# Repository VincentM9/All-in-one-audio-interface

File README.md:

# All-in-one audio interface

A USB DAC / headphone amplifier with a phantom-powered microphone input,
built one block at a time. Each block is designed, drawn in Altium, built and
tested on its own before the next one starts.

## Goal

- Headphone output: **at least 2 W into 32 Ω** single-ended, plus balanced outputs (4.4 mm and 4-pin XLR)
- USB DAC for playback
- XLR microphone input with 48 V phantom power for condenser mics

## Blocks

| # | Block | Status |
|---|---|---|
| 1 | [Balanced headphone amplifier](docs/01-headphone-amp.md): line in → ~8.9 W @ 32 Ω balanced (4.4 mm + 4-pin XLR), ~2.5 W single-ended (6.35 mm), from a bench ±16 V supply | **designing** |
| 2 | Power supply: DC jack → ±16 V at 1.2 A per rail for the amp | not started |
| 3 | USB DAC: USB → line out | not started |
| 4 | Mic preamp with 48 V phantom | not started |
| 5 | Put it together: one board, one enclosure | not started |

The earlier all-in-one attempt (full schematic, generated PCB) is in git
history before this commit, if any part of it is ever useful again.

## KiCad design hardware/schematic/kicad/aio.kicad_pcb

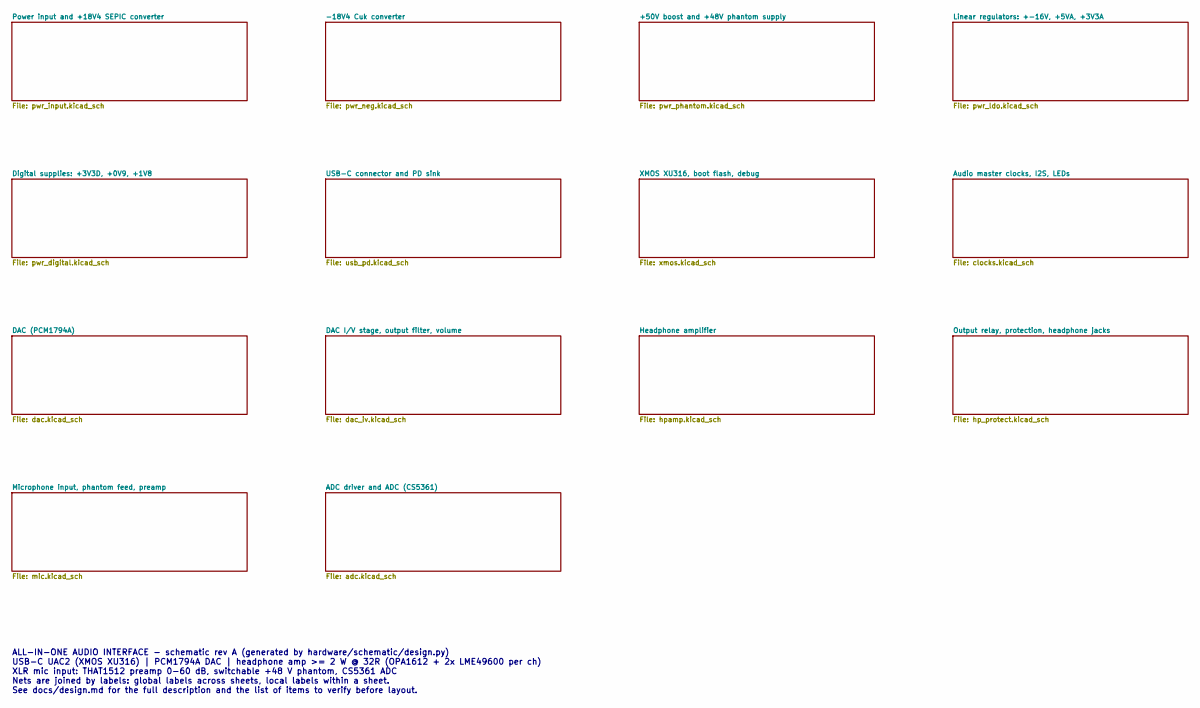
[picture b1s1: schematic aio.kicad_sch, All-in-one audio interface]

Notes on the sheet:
ALL-IN-ONE AUDIO INTERFACE - schematic rev A (generated by hardware/schematic/design.py) USB-C UAC2 (XMOS XU316) | PCM1794A DAC | headphone amp >= 2 W @ 32R (OPA1612 + 2x LME49600 per ch) XLR mic input: THAT1512 preamp 0-60 dB, switchable +48 V phantom, CS5361 ADC Nets are joined by labels: global 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

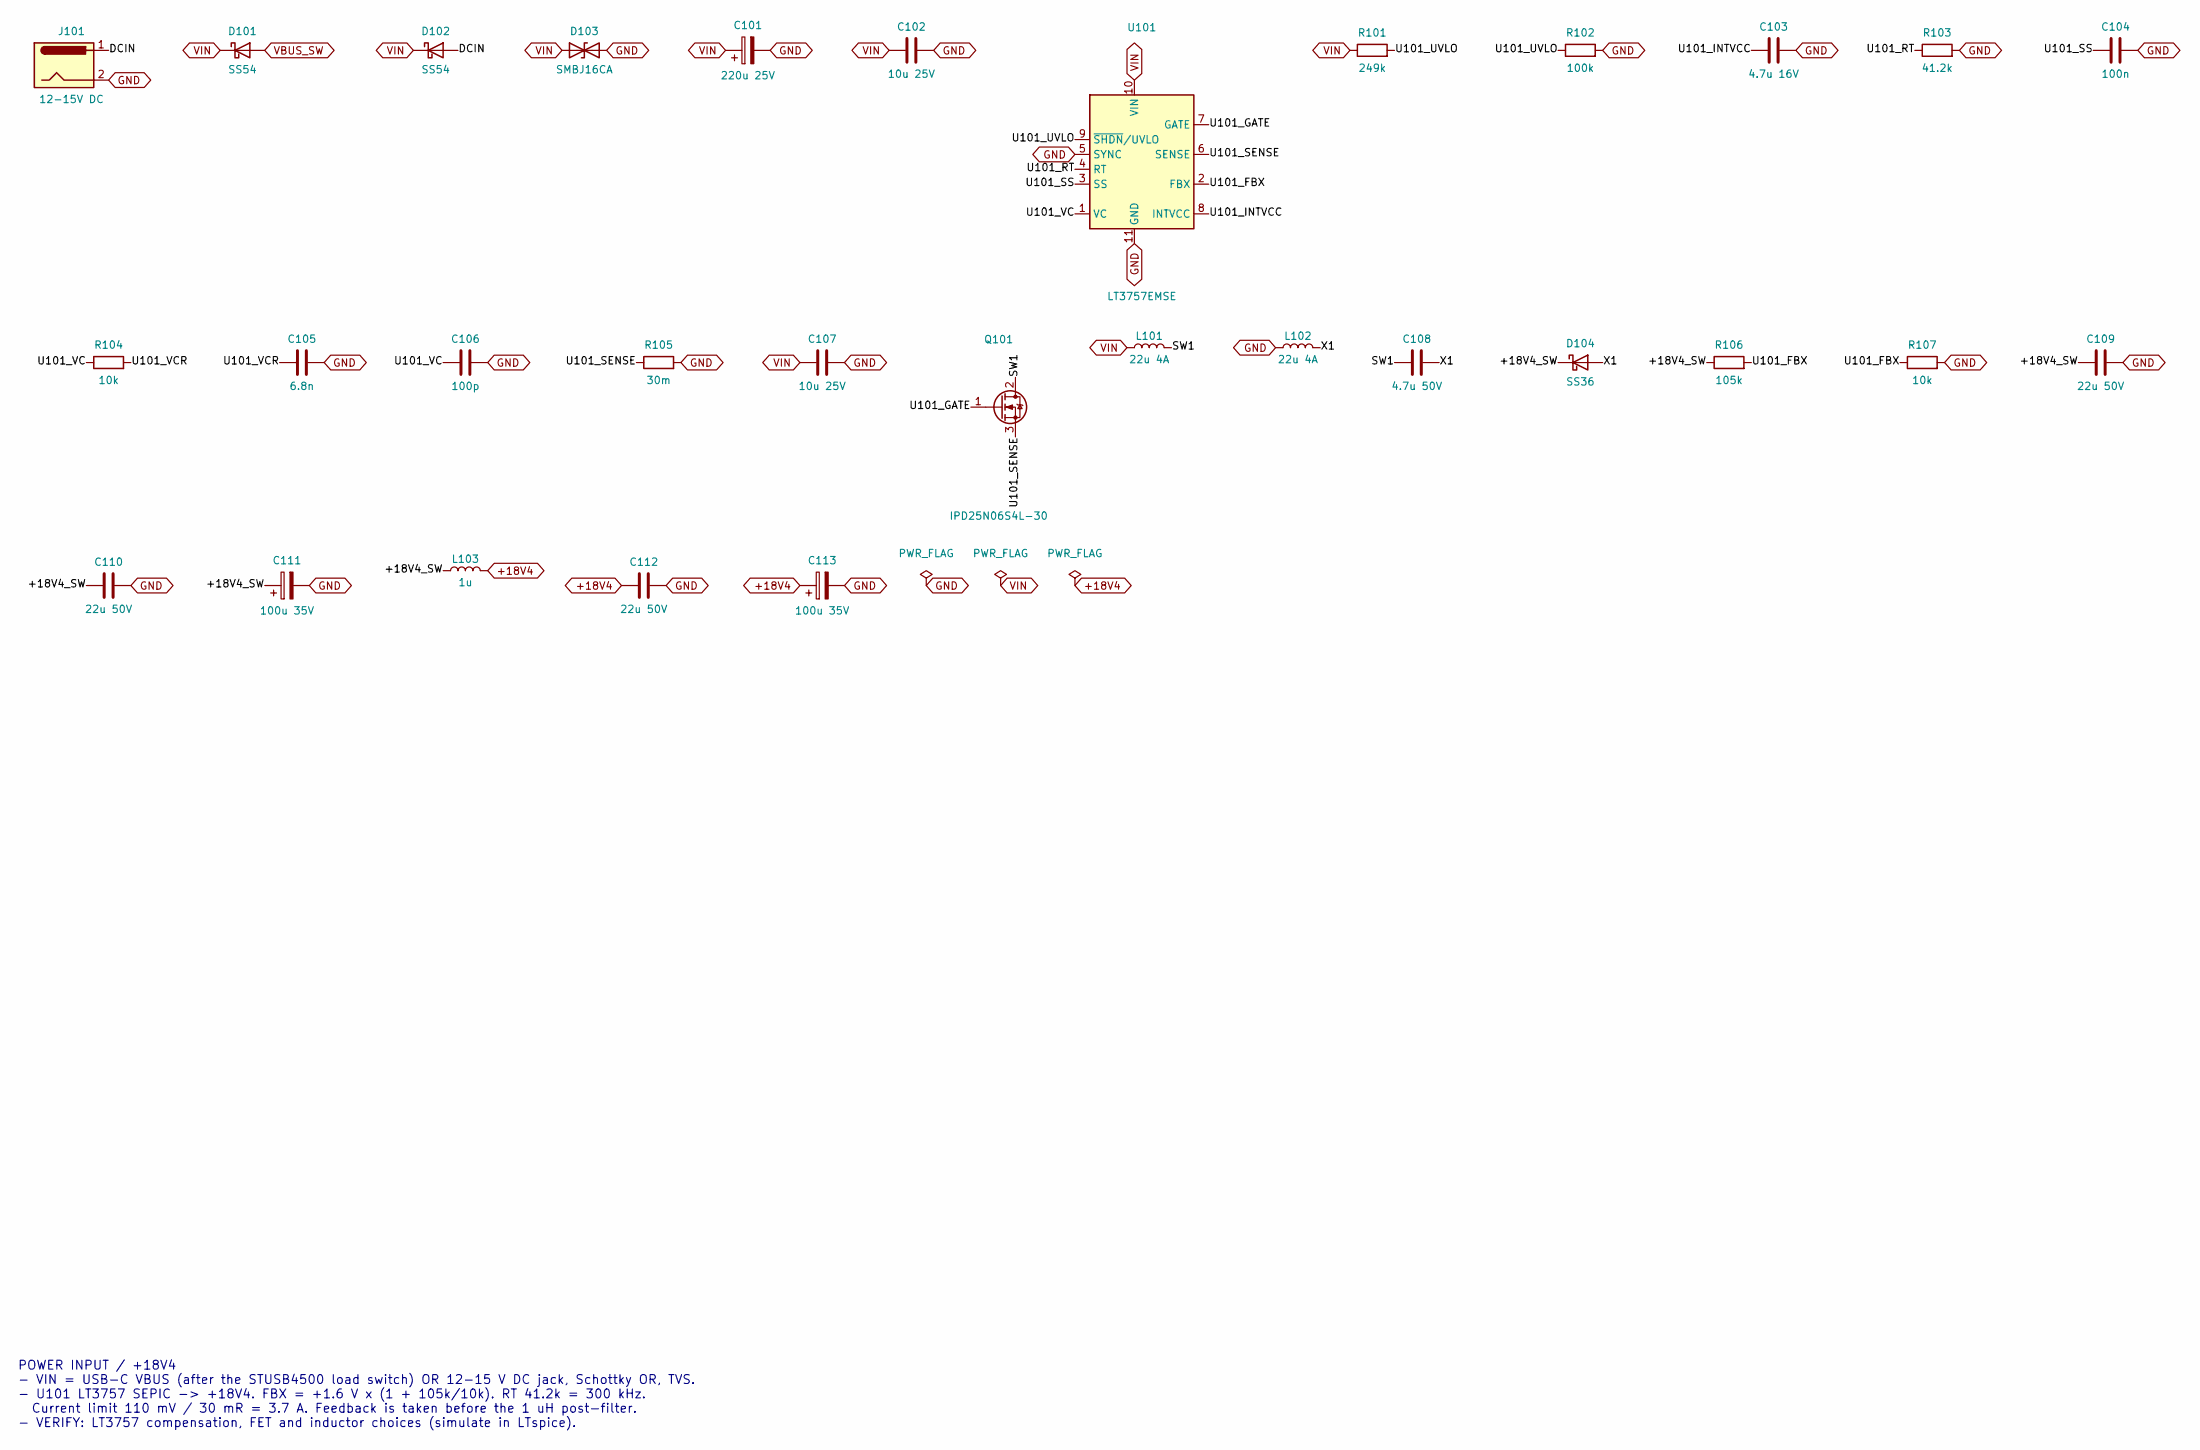
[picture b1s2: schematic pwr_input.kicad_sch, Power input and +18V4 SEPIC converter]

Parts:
C101: 220u 25V; CP_Elec_10x10
C102, C107: 10u 25V; C_1210_3225Metric
C103: 4.7u 16V; C_0805_2012Metric
C104: 100n; C_0603_1608Metric
C105: 6.8n; C_0603_1608Metric
C106: 100p; C_0603_1608Metric
C108: 4.7u 50V; C_1210_3225Metric
C109, C110, C112: 22u 50V; C_1210_3225Metric
C111, C113: 100u 35V; CP_Elec_8x10
D101, D102: SS54; D_SMB; MPN SS54
D103: SMBJ16CA; D_SMB; MPN SMBJ16CA
D104: SS36; D_SMB; MPN SS36
J101: 12-15V DC; BarrelJack_Horizontal; MPN PJ-102AH
L101, L102: 22u 4A; L_Bourns_SRR1260; MPN SRR1260-220M
L103: 1u; L_1210_3225Metric
Q101: IPD25N06S4L-30; TO-252-2; MPN IPD25N06S4L-30
R101: 249k; R_0603_1608Metric
R102: 100k; R_0603_1608Metric
R103: 41.2k; R_0603_1608Metric
R104, R107: 10k; R_0603_1608Metric
R105: 30m; R_2512_6332Metric
R106: 105k; R_0603_1608Metric
U101: LT3757EMSE; MSOP-10-1EP_3x3mm_P0.5mm_EP1.68x1.88mm; MPN LT3757EMSE#PBF

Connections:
+18V4: C112.1, C113.1, L103.2; also elsewhere on the board
+18V4_SW: C109.1, C110.1, C111.1, D104.1 (K), L103.1, R106.1
DCIN: D102.2 (A), J101.1
GND: C101.2, C102.2, C103.2, C104.2, C105.2, C106.2, C107.2, C109.2, C110.2, C111.2, C112.2, C113.2, D103.2 (A2), J101.2, L102.1, R102.2, R103.2, R105.2, R107.2, U101.5 (SYNC), U101.11 (GND); also elsewhere on the board
SW1: C108.1, L101.2, Q101.2 (D)
U101_FBX: R106.2, R107.1, U101.2 (FBX)
U101_GATE: Q101.1 (G), U101.7 (GATE)
U101_INTVCC: C103.1, U101.8 (INTVCC)
U101_RT: R103.1, U101.4 (RT)
U101_SENSE: Q101.3 (S), R105.1, U101.6 (SENSE)
U101_SS: C104.1, U101.3 (SS)
U101_UVLO: R101.2, R102.1, U101.9 (~SHDN/UVLO)
U101_VC: C106.1, R104.1, U101.1 (VC)
U101_VCR: C105.1, R104.2
VBUS_SW: D101.2 (A); also elsewhere on the board
VIN: C101.1, C102.1, C107.1, D101.1 (K), D102.1 (K), D103.1 (A1), L101.1, R101.1, U101.10 (VIN); also elsewhere on the board
X1: C108.2, D104.2 (A), L102.2

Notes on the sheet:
POWER INPUT / +18V4 - VIN = USB-C VBUS (after the STUSB4500 load switch) OR 12-15 V DC jack, Schottky OR, TVS. - U101 LT3757 SEPIC -> +18V4. FBX = +1.6 V x (1 + 105k/10k). RT 41.2k = 300 kHz. Current limit 110 mV / 30 mR = 3.7 A. Feedback is taken before the 1 uH post-filter. - VERIFY: LT3757 compe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

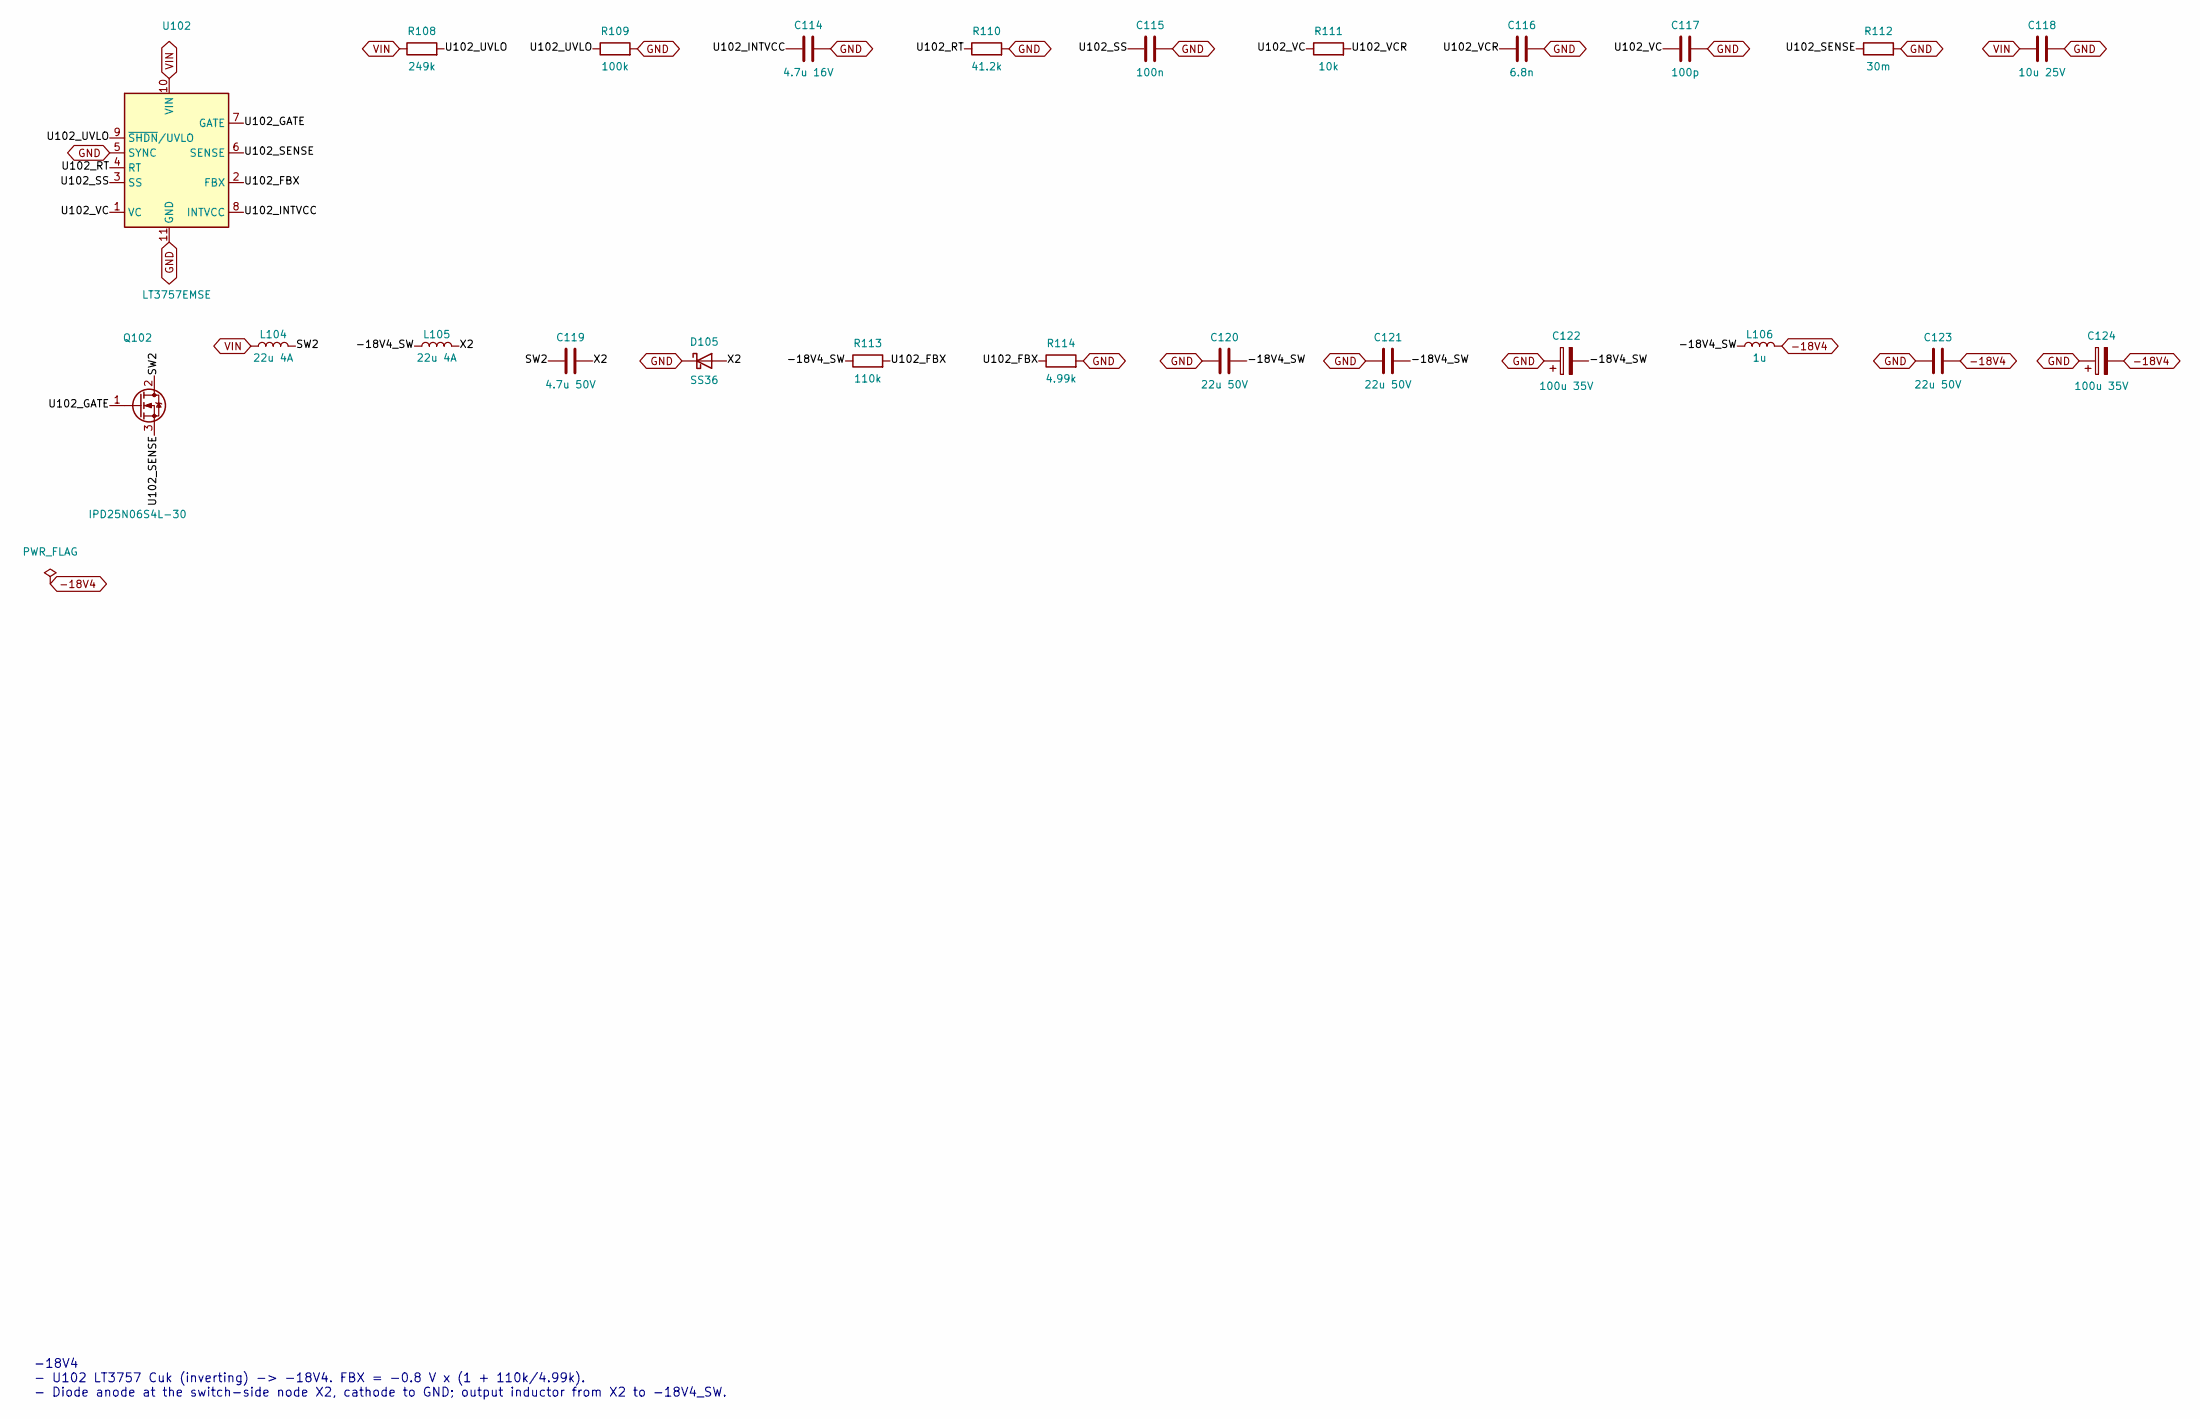
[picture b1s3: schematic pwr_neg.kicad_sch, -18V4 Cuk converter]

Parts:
C114: 4.7u 16V; C_0805_2012Metric
C115: 100n; C_0603_1608Metric
C116: 6.8n; C_0603_1608Metric
C117: 100p; C_0603_1608Metric
C118: 10u 25V; C_1210_3225Metric
C119: 4.7u 50V; C_1210_3225Metric
C120, C121, C123: 22u 50V; C_1210_3225Metric
C122, C124: 100u 35V; CP_Elec_8x10
D105: SS36; D_SMB; MPN SS36
L104, L105: 22u 4A; L_Bourns_SRR1260; MPN SRR1260-220M
L106: 1u; L_1210_3225Metric
Q102: IPD25N06S4L-30; TO-252-2; MPN IPD25N06S4L-30
R108: 249k; R_0603_1608Metric
R109: 100k; R_0603_1608Metric
R110: 41.2k; R_0603_1608Metric
R111: 10k; R_0603_1608Metric
R112: 30m; R_2512_6332Metric
R113: 110k; R_0603_1608Metric
R114: 4.99k; R_0603_1608Metric
U102: LT3757EMSE; MSOP-10-1EP_3x3mm_P0.5mm_EP1.68x1.88mm; MPN LT3757EMSE#PBF

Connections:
-18V4: C123.2, C124.2, L106.2; also elsewhere on the board
-18V4_SW: C120.2, C121.2, C122.2, L105.1, L106.1, R113.1
GND: C114.2, C115.2, C116.2, C117.2, C118.2, C120.1, C121.1, C122.1, C123.1, C124.1, D105.1 (K), R109.2, R110.2, R112.2, R114.2, U102.5 (SYNC), U102.11 (GND); also elsewhere on the board
SW2: C119.1, L104.2, Q102.2 (D)
U102_FBX: R113.2, R114.1, U102.2 (FBX)
U102_GATE: Q102.1 (G), U102.7 (GATE)
U102_INTVCC: C114.1, U102.8 (INTVCC)
U102_RT: R110.1, U102.4 (RT)
U102_SENSE: Q102.3 (S), R112.1, U102.6 (SENSE)
U102_SS: C115.1, U102.3 (SS)
U102_UVLO: R108.2, R109.1, U102.9 (~SHDN/UVLO)
U102_VC: C117.1, R111.1, U102.1 (VC)
U102_VCR: C116.1, R111.2
VIN: C118.1, L104.1, R108.1, U102.10 (VIN); also elsewhere on the board
X2: C119.2, D105.2 (A), L105.2

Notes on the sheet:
-18V4 - U102 LT3757 Cuk (inverting) -> -18V4. FBX = -0.8 V x (1 + 110k/4.99k). - Diode anode at the switch-side node X2, cathode to GND; output inductor from X2 to -18V4_SW.

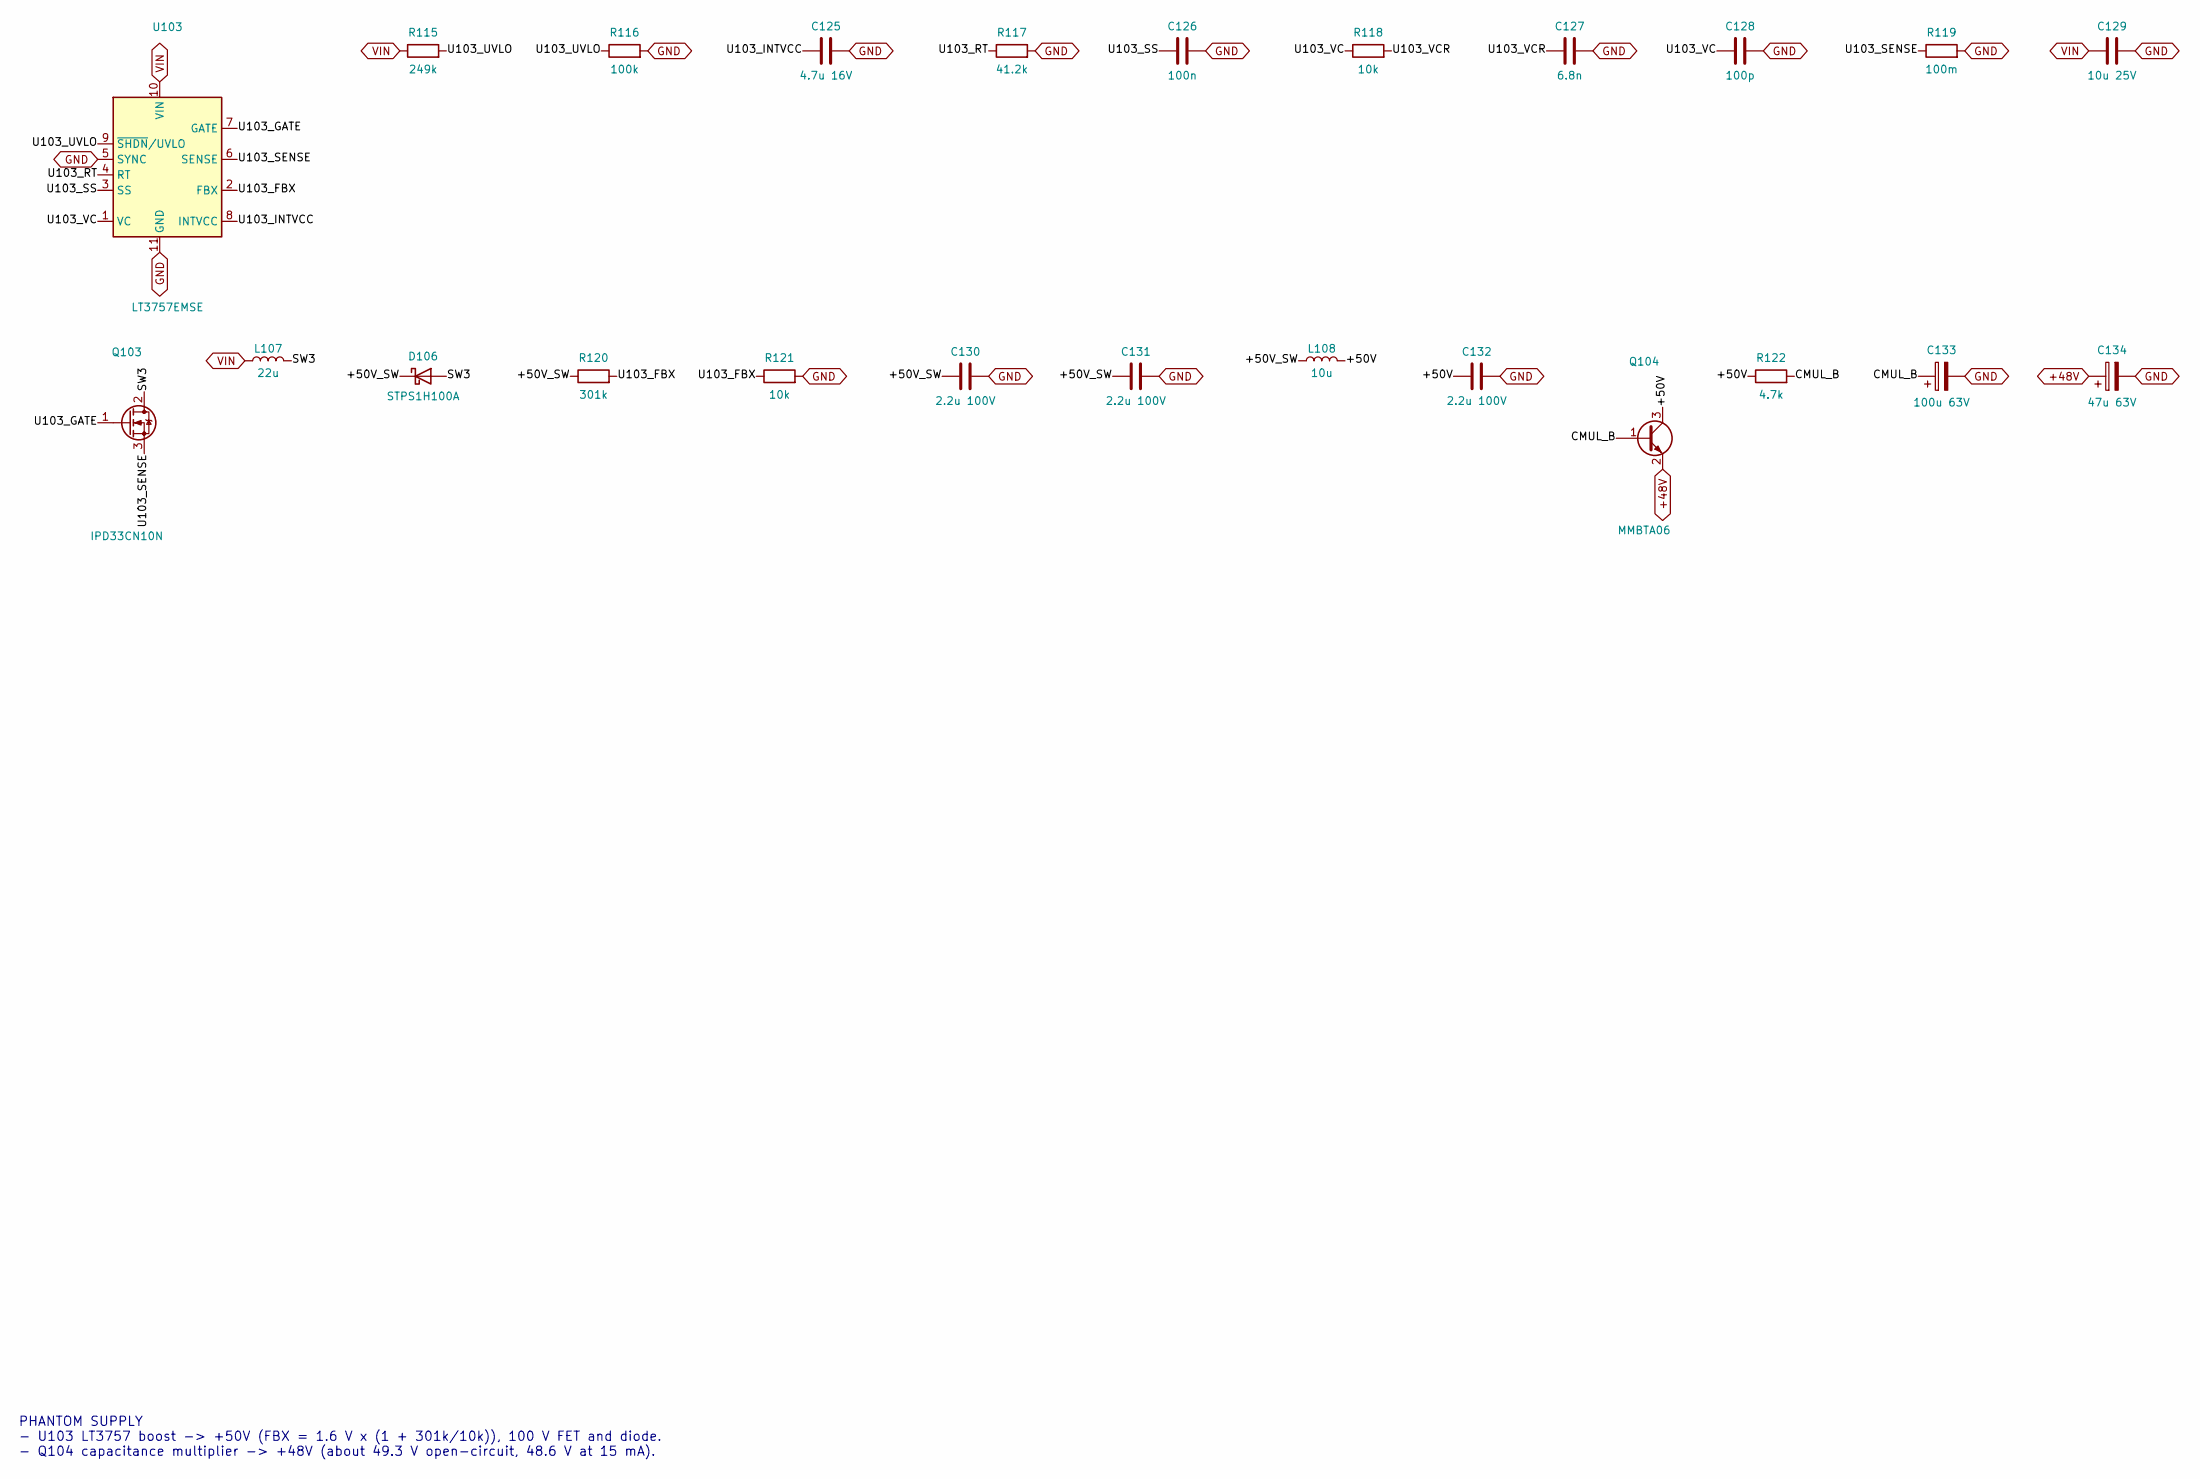
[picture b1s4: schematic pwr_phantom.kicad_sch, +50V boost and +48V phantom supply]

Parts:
C125: 4.7u 16V; C_0805_2012Metric
C126: 100n; C_0603_1608Metric
C127: 6.8n; C_0603_1608Metric
C128: 100p; C_0603_1608Metric
C129: 10u 25V; C_1210_3225Metric
C130, C131, C132: 2.2u 100V; C_1210_3225Metric
C133: 100u 63V; CP_Elec_10x10
C134: 47u 63V; CP_Elec_10x10
D106: STPS1H100A; D_SMA; MPN STPS1H100A
L107: 22u; L_Bourns_SRR1260
L108: 10u; L_1210_3225Metric
Q103: IPD33CN10N; TO-252-2; MPN IPD33CN10N G
Q104: MMBTA06; SOT-23; MPN MMBTA06
R115: 249k; R_0603_1608Metric
R116: 100k; R_0603_1608Metric
R117: 41.2k; R_0603_1608Metric
R118, R121: 10k; R_0603_1608Metric
R119: 100m; R_2512_6332Metric
R120: 301k; R_0603_1608Metric
R122: 4.7k; R_0603_1608Metric
U103: LT3757EMSE; MSOP-10-1EP_3x3mm_P0.5mm_EP1.68x1.88mm; MPN LT3757EMSE#PBF

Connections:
+48V: C134.1, Q104.2 (E); also elsewhere on the board
+50V: C132.1, L108.2, Q104.3 (C), R122.1
+50V_SW: C130.1, C131.1, D106.1 (K), L108.1, R120.1
CMUL_B: C133.1, Q104.1 (B), R122.2
GND: C125.2, C126.2, C127.2, C128.2, C129.2, C130.2, C131.2, C132.2, C133.2, C134.2, R116.2, R117.2, R119.2, R121.2, U103.5 (SYNC), U103.11 (GND); also elsewhere on the board
SW3: D106.2 (A), L107.2, Q103.2 (D)
U103_FBX: R120.2, R121.1, U103.2 (FBX)
U103_GATE: Q103.1 (G), U103.7 (GATE)
U103_INTVCC: C125.1, U103.8 (INTVCC)
U103_RT: R117.1, U103.4 (RT)
U103_SENSE: Q103.3 (S), R119.1, U103.6 (SENSE)
U103_SS: C126.1, U103.3 (SS)
U103_UVLO: R115.2, R116.1, U103.9 (~SHDN/UVLO)
U103_VC: C128.1, R118.1, U103.1 (VC)
U103_VCR: C127.1, R118.2
VIN: C129.1, L107.1, R115.1, U103.10 (VIN); also elsewhere on the board

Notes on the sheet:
PHANTOM SUPPLY - U103 LT3757 boost -> +50V (FBX = 1.6 V x (1 + 301k/10k)), 100 V FET and diode. - Q104 capacitance multiplier -> +48V (about 49.3 V open-circuit, 48.6 V at 15 mA).

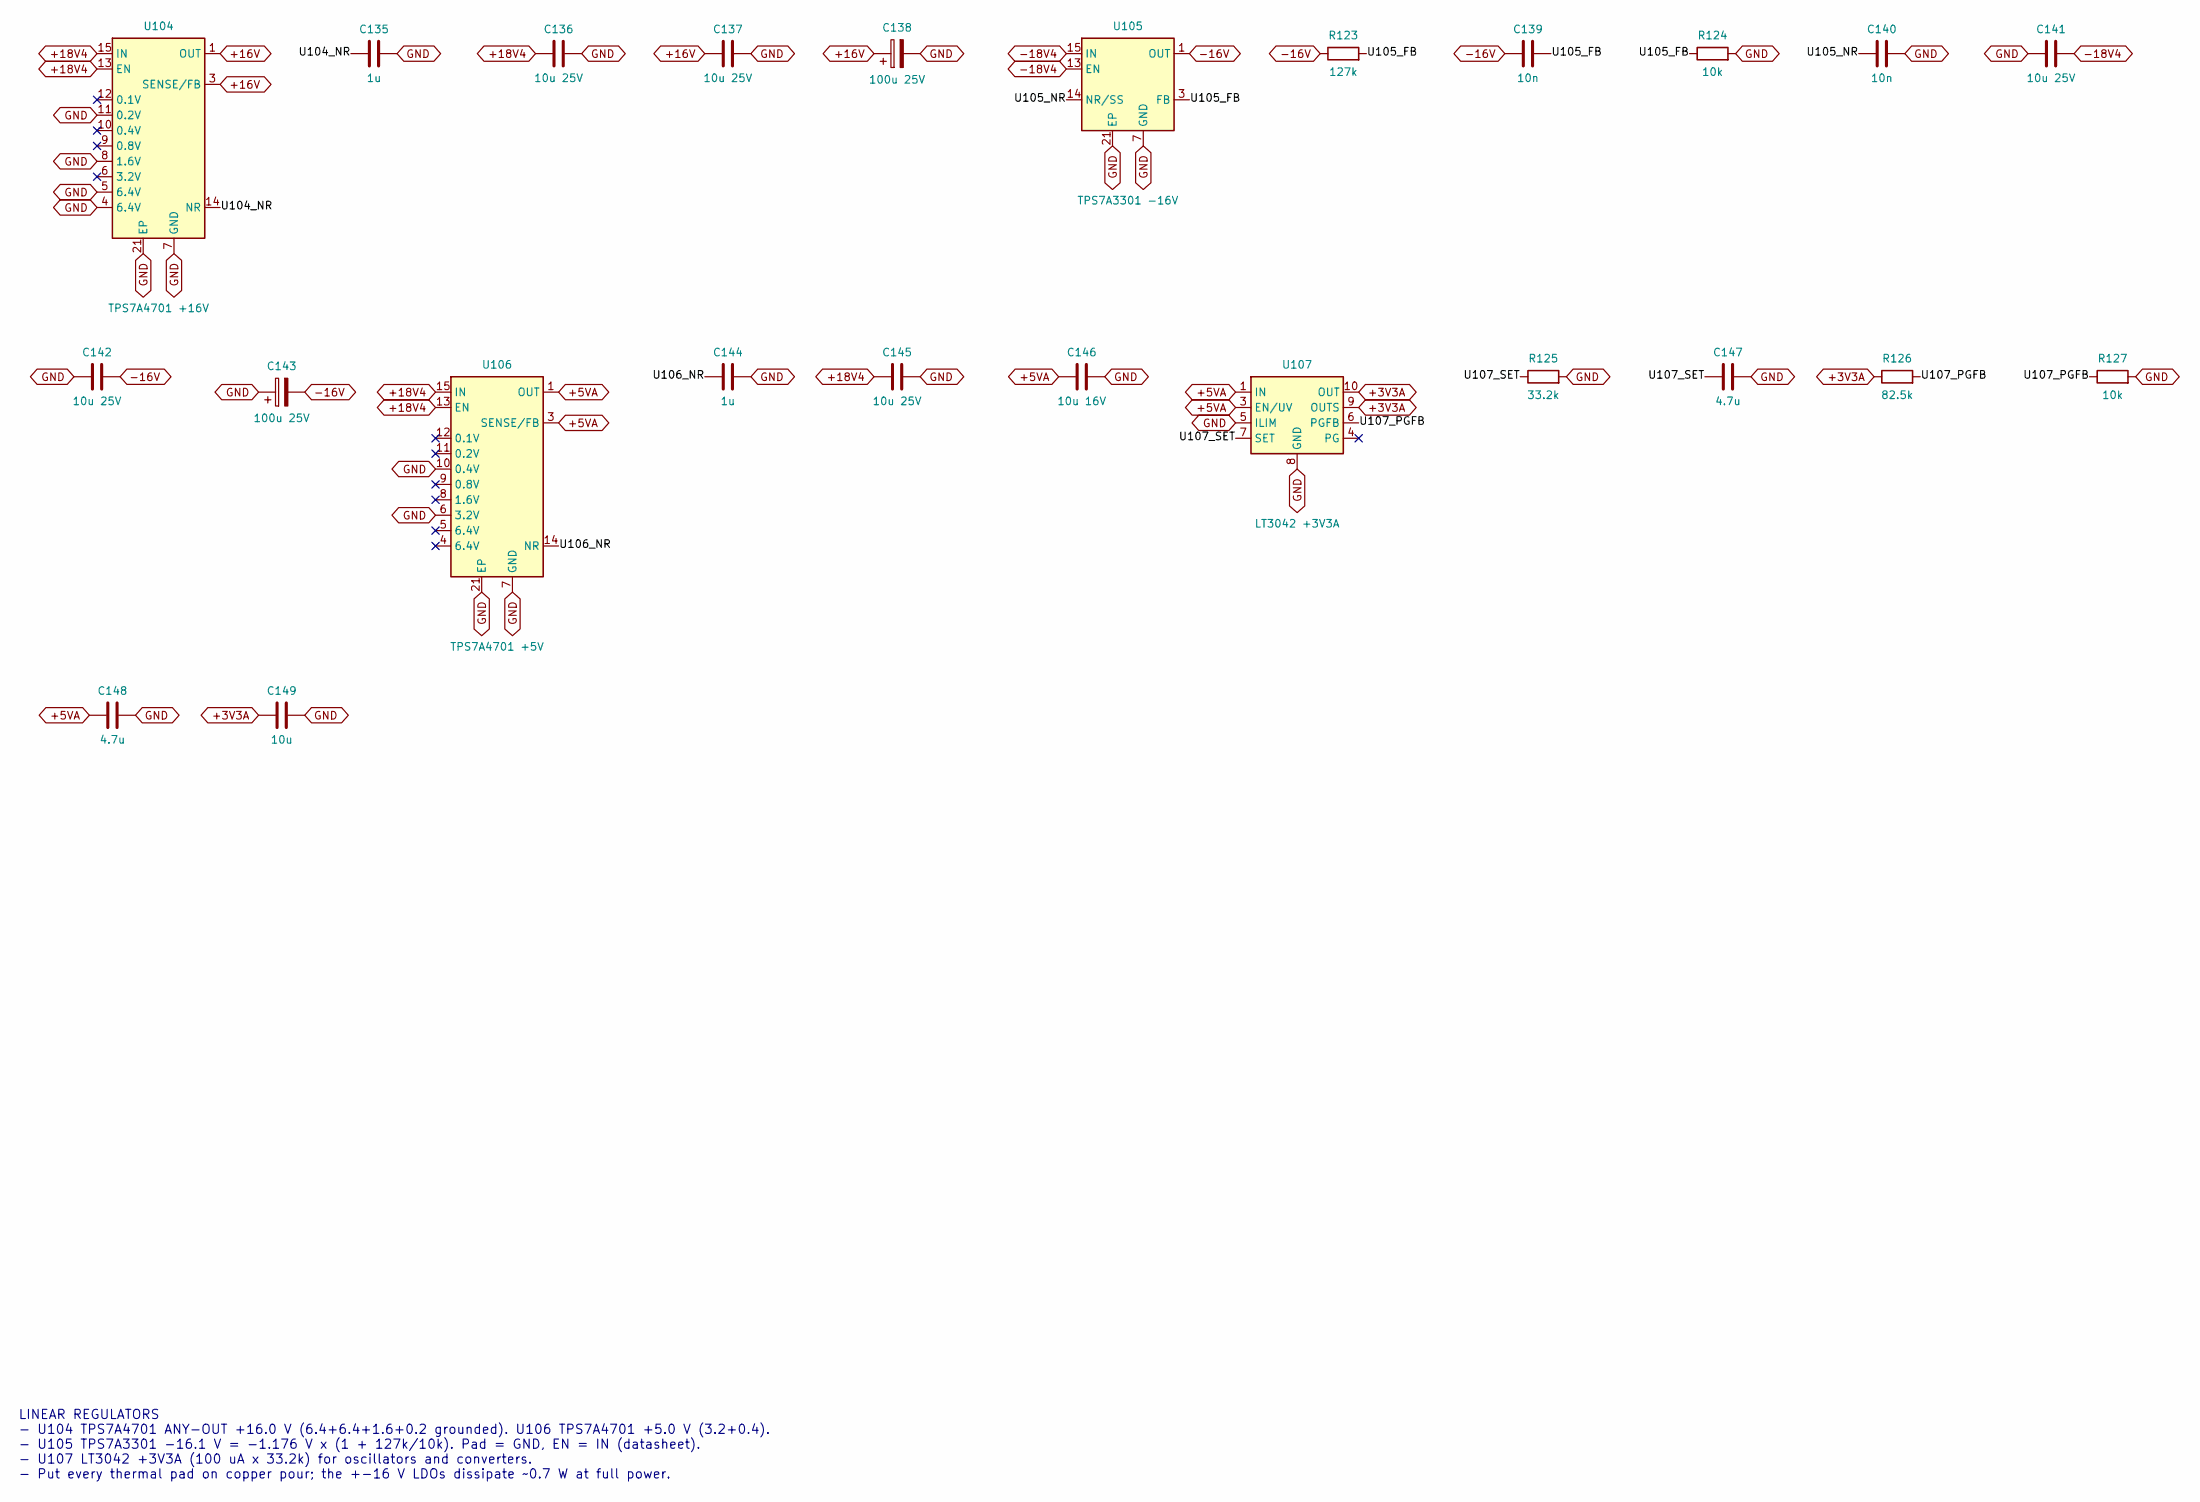
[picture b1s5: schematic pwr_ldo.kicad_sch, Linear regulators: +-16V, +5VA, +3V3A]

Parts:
C135, C144: 1u; C_0603_1608Metric
C136, C137, C141, C142, C145: 10u 25V; C_1210_3225Metric
C138, C143: 100u 25V; CP_Elec_8x10
C139, C140: 10n; C_0603_1608Metric
C146: 10u 16V; C_1206_3216Metric
C147, C148: 4.7u; C_0805_2012Metric
C149: 10u; C_0805_2012Metric
R123: 127k; R_0603_1608Metric
R124, R127: 10k; R_0603_1608Metric
R125: 33.2k; R_0603_1608Metric
R126: 82.5k; R_0603_1608Metric
U104: TPS7A4701 +16V; Texas_RGW0020A_VQFN-20-1EP_5x5mm_P0.65mm_EP3.15x3.15mm_Ther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; MPN TPS7A4701RGWR
U105: TPS7A3301 -16V; Texas_RGW0020A_VQFN-20-1EP_5x5mm_P0.65mm_EP3.15x3.15mm_Ther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; MPN TPS7A3301RGWR
U106: TPS7A4701 +5V; Texas_RGW0020A_VQFN-20-1EP_5x5mm_P0.65mm_EP3.15x3.15mm_Ther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; MPN TPS7A4701RGWR
U107: LT3042 +3V3A; MSOP-10-1EP_3x3mm_P0.5mm_EP1.68x1.88mm; MPN LT3042EMSE#PBF

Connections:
+3V3A: C149.1, R126.1, U107.9 (OUTS), U107.10 (OUT); also elsewhere on the board
+5VA: C146.1, C148.1, U106.1 (OUT), U106.3 (SENSE/FB), U106.20 (OUT), U107.1 (IN), U107.2 (IN), U107.3 (EN/UV); also elsewhere on the board
+16V: C137.1, C138.1, U104.1 (OUT), U104.3 (SENSE/FB), U104.20 (OUT); also elsewhere on the board
+18V4: C136.1, C145.1, U104.13 (EN), U104.15 (IN), U104.16 (IN), U106.13 (EN), U106.15 (IN), U106.16 (IN); also elsewhere on the board
-16V: C139.1, C142.2, C143.2, R123.1, U105.1 (OUT), U105.20 (OUT); also elsewhere on the board
-18V4: C141.2, U105.13 (EN), U105.15 (IN), U105.16 (IN); also elsewhere on the board
GND: C135.2, C136.2, C137.2, C138.2, C140.2, C141.1, C142.1, C143.1, C144.2, C145.2, C146.2, C147.2, C148.2, C149.2, R124.2, R125.2, R127.2, U104.4 (6.4V), U104.5 (6.4V), U104.7 (GND), U104.8 (1.6V), U104.11 (0.2V), U104.21 (EP), U105.7 (GND), U105.21 (EP), U106.6 (3.2V), U106.7 (GND), U106.10 (0.4V), U106.21 (EP), U107.5 (ILIM), U107.8 (GND), U107.11 (GND); also elsewhere on the board
U104_NR: C135.1, U104.14 (NR)
U105_FB: C139.2, R123.2, R124.1, U105.3 (FB)
U105_NR: C140.1, U105.14 (NR/SS)
U106_NR: C144.1, U106.14 (NR)
U107_PGFB: R126.2, R127.1, U107.6 (PGFB)
U107_SET: C147.1, R125.1, U107.7 (SET)

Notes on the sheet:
LINEAR REGULATORS - U104 TPS7A4701 ANY-OUT +16.0 V (6.4+6.4+1.6+0.2 grounded). U106 TPS7A4701 +5.0 V (3.2+0.4). - U105 TPS7A3301 -16.1 V = -1.176 V x (1 + 127k/10k). Pad = GND, EN = IN (datasheet). - U107 LT3042 +3V3A (100 uA x 33.2k) for oscillators and converters. - Put every thermal pad on coppe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

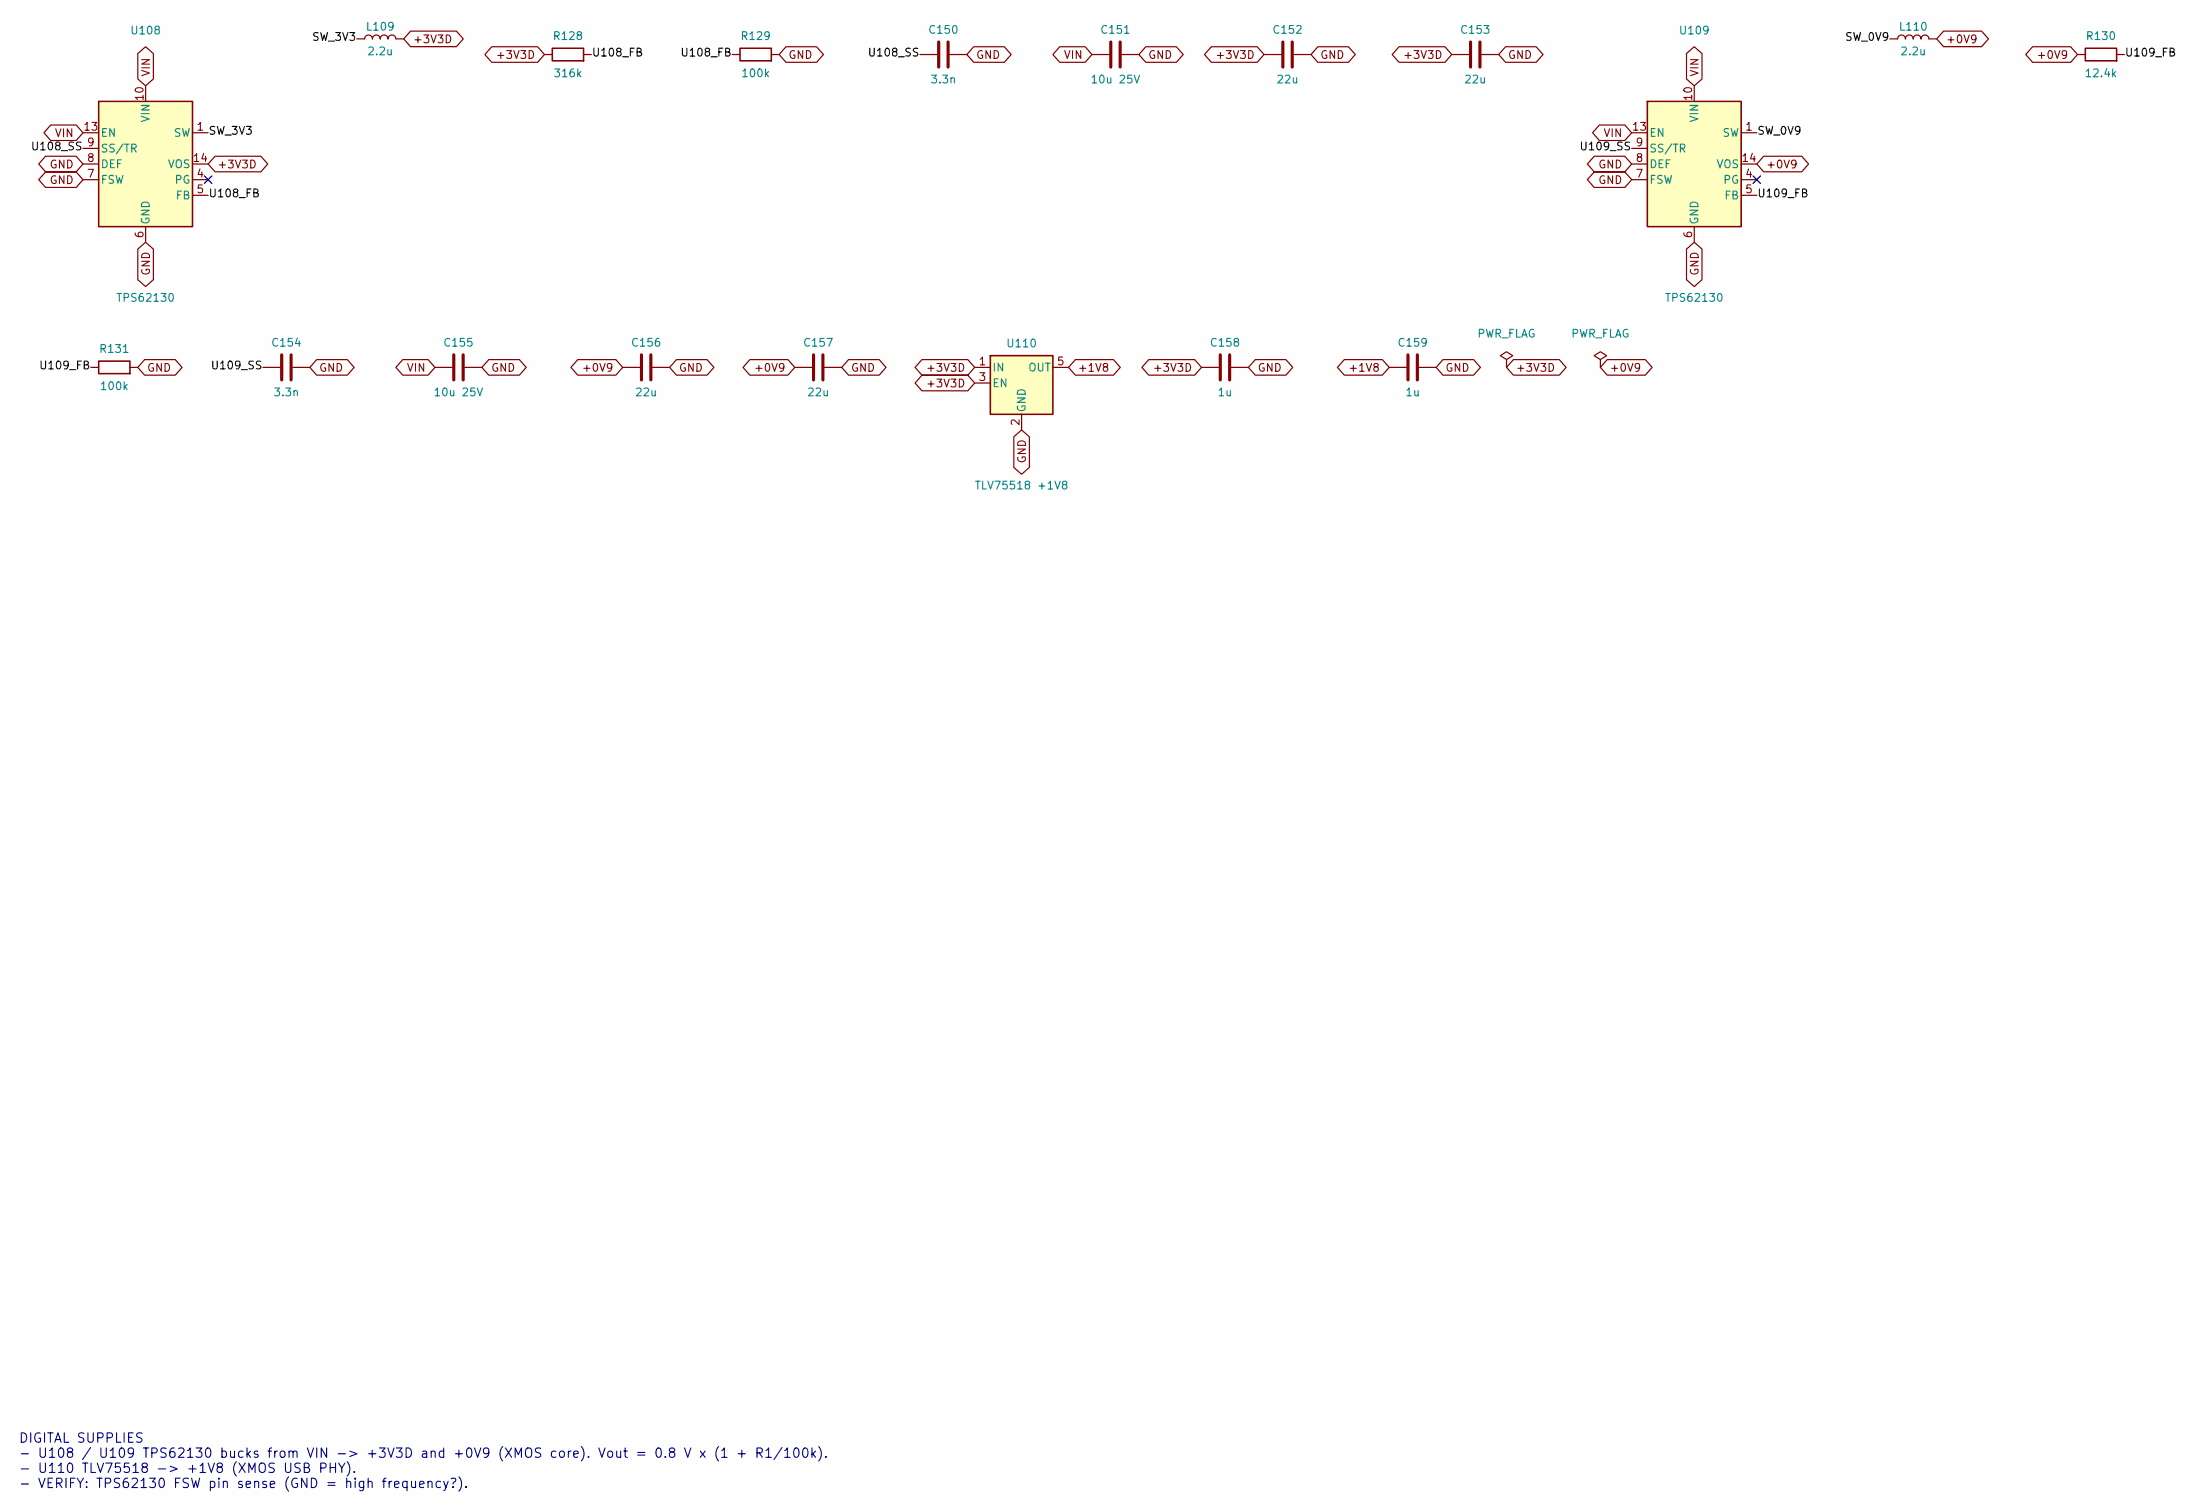
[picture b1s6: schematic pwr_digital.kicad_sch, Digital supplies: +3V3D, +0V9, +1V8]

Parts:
C150, C154: 3.3n; C_0603_1608Metric
C151, C155: 10u 25V; C_1210_3225Metric
C152, C153, C156, C157: 22u; C_0805_2012Metric
C158, C159: 1u; C_0603_1608Metric
L109, L110: 2.2u; L_Bourns_SRP5030T; MPN SRP5030T-2R2M
R128: 316k; R_0603_1608Metric
R129, R131: 100k; R_0603_1608Metric
R130: 12.4k; R_0603_1608Metric
U108, U109: TPS62130; VQFN-16-1EP_3x3mm_P0.5mm_EP1.68x1.68mm_ThermalVias; MPN TPS62130RGTR
U110: TLV75518 +1V8; SOT-23-5; MPN TLV75518PDBVR

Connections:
+0V9: C156.1, C157.1, L110.2, R130.1, U109.14 (VOS); also elsewhere on the board
+1V8: C159.1, U110.5 (OUT); also elsewhere on the board
+3V3D: C152.1, C153.1, C158.1, L109.2, R128.1, U108.14 (VOS), U110.1 (IN), U110.3 (EN); also elsewhere on the board
GND: C150.2, C151.2, C152.2, C153.2, C154.2, C155.2, C156.2, C157.2, C158.2, C159.2, R129.2, R131.2, U108.6 (GND), U108.7 (FSW), U108.8 (DEF), U108.15 (GND), U108.16 (GND), U108.17 (GND), U109.6 (GND), U109.7 (FSW), U109.8 (DEF), U109.15 (GND), U109.16 (GND), U109.17 (GND), U110.2 (GND); also elsewhere on the board
SW_0V9: L110.1, U109.1 (SW), U109.2 (SW), U109.3 (SW)
SW_3V3: L109.1, U108.1 (SW), U108.2 (SW), U108.3 (SW)
U108_FB: R128.2, R129.1, U108.5 (FB)
U108_SS: C150.1, U108.9 (SS/TR)
U109_FB: R130.2, R131.1, U109.5 (FB)
U109_SS: C154.1, U109.9 (SS/TR)
VIN: C151.1, C155.1, U108.10 (VIN), U108.11 (VIN), U108.12 (VIN), U108.13 (EN), U109.10 (VIN), U109.11 (VIN), U109.12 (VIN), U109.13 (EN); also elsewhere on the board

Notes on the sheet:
DIGITAL SUPPLIES - U108 / U109 TPS62130 bucks from VIN -> +3V3D and +0V9 (XMOS core). Vout = 0.8 V x (1 + R1/100k). - U110 TLV75518 -> +1V8 (XMOS USB PHY). - VERIFY: TPS62130 FSW pin sense (GND = high frequency?).
